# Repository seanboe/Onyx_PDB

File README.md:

# Onyx Power Distribution Board 

See the updated project in [Team Inspiration's Repository](https://github.com/InspirationRobotics/PowerDist).

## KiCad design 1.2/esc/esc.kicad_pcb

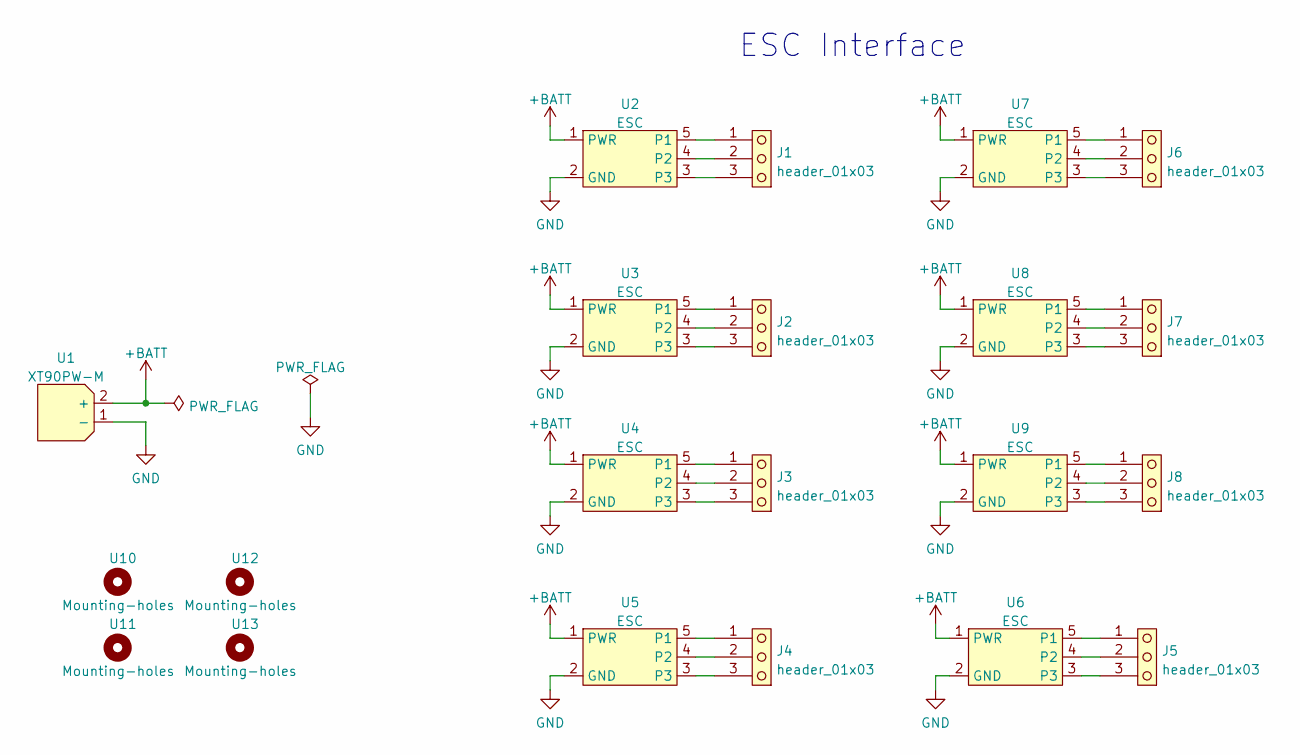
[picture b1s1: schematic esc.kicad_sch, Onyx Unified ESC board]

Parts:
J1, J2, J3, J4, J5, J6, J7, J8: header_01x03; MegaF_RAH_Single_3x5.7mm
U1: XT90PW-M; AMASS_XT90PW-M_Horizontal
U2, U3, U4, U5, U6, U7, U8, U9: ESC; esc
U10, U11, U12, U13: Mounting-holes; plated_hole_3.0x3.6mm

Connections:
+BATT: U1.2 (+), U2.1 (PWR), U3.1 (PWR), U4.1 (PWR), U5.1 (PWR), U6.1 (PWR), U7.1 (PWR), U8.1 (PWR), U9.1 (PWR)
GND: U1.1 (-), U2.2 (GND), U3.2 (GND), U4.2 (GND), U5.2 (GND), U6.2 (GND), U7.2 (GND), U8.2 (GND), U9.2 (GND)
unnamed: J1.1, U2.5 (P1)
unnamed: J1.2, U2.4 (P2)
unnamed: J1.3, U2.3
unnamed: J2.1, U3.5 (P1)
unnamed: J2.2, U3.4 (P2)
unnamed: J2.3, U3.3
unnamed: J3.1, U4.5 (P1)
unnamed: J3.2, U4.4 (P2)
unnamed: J3.3, U4.3
unnamed: J4.1, U5.5 (P1)
unnamed: J4.2, U5.4 (P2)
unnamed: J4.3, U5.3
unnamed: J5.1, U6.5 (P1)
unnamed: J5.2, U6.4 (P2)
unnamed: J5.3, U6.3
unnamed: J6.1, U7.5 (P1)
unnamed: J6.2, U7.4 (P2)
unnamed: J6.3, U7.3
unnamed: J7.1, U8.5 (P1)
unnamed: J7.2, U8.4 (P2)
unnamed: J7.3, U8.3
unnamed: J8.1, U9.5 (P1)
unnamed: J8.2, U9.4 (P2)
unnamed: J8.3, U9.3

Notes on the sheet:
ESC Interface

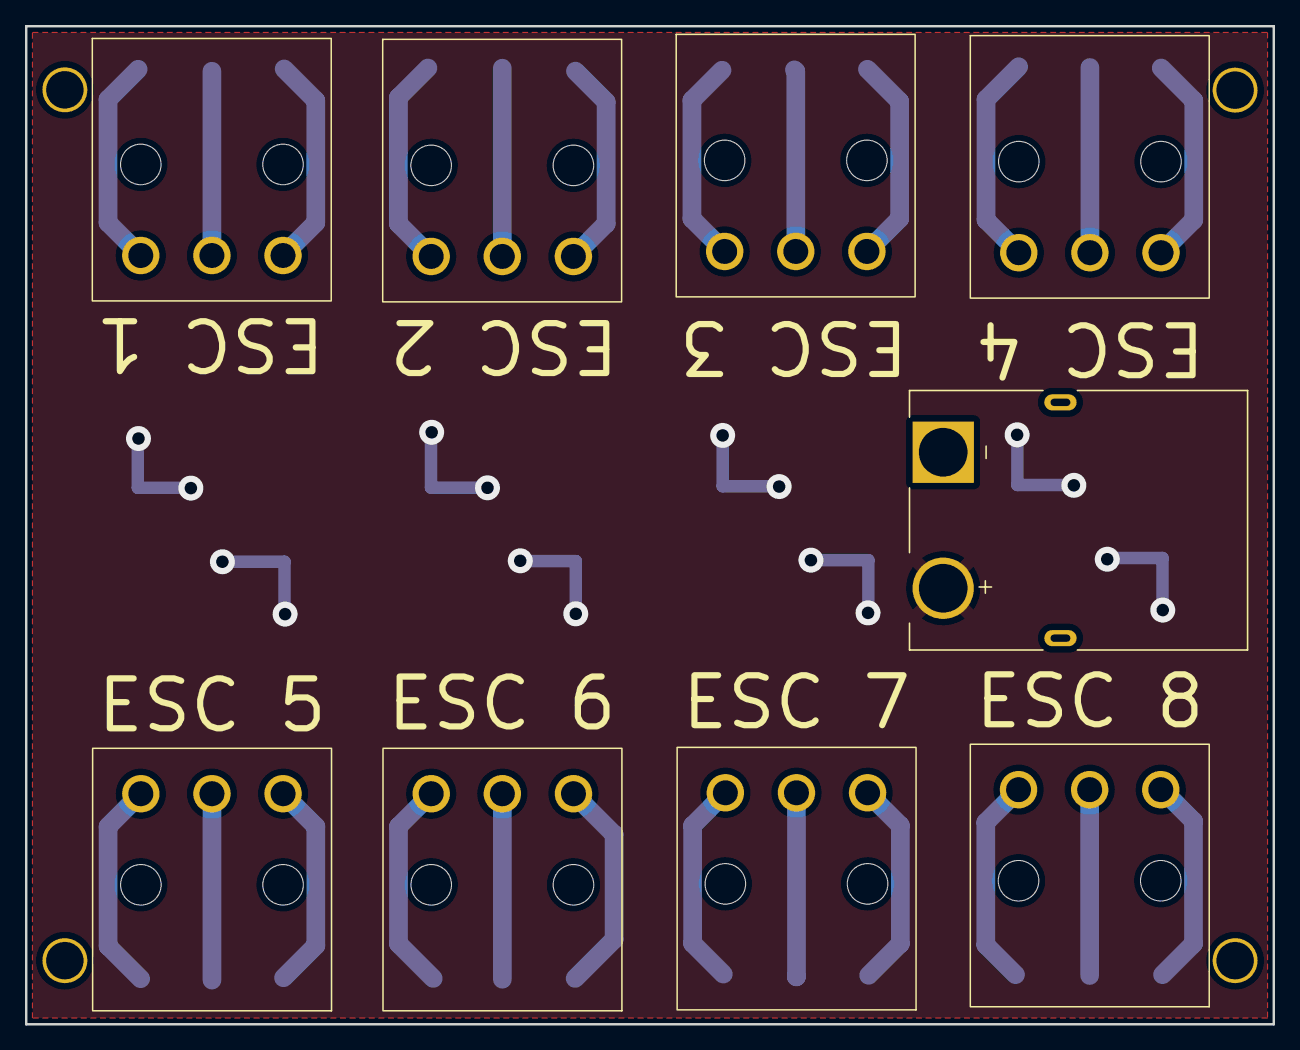
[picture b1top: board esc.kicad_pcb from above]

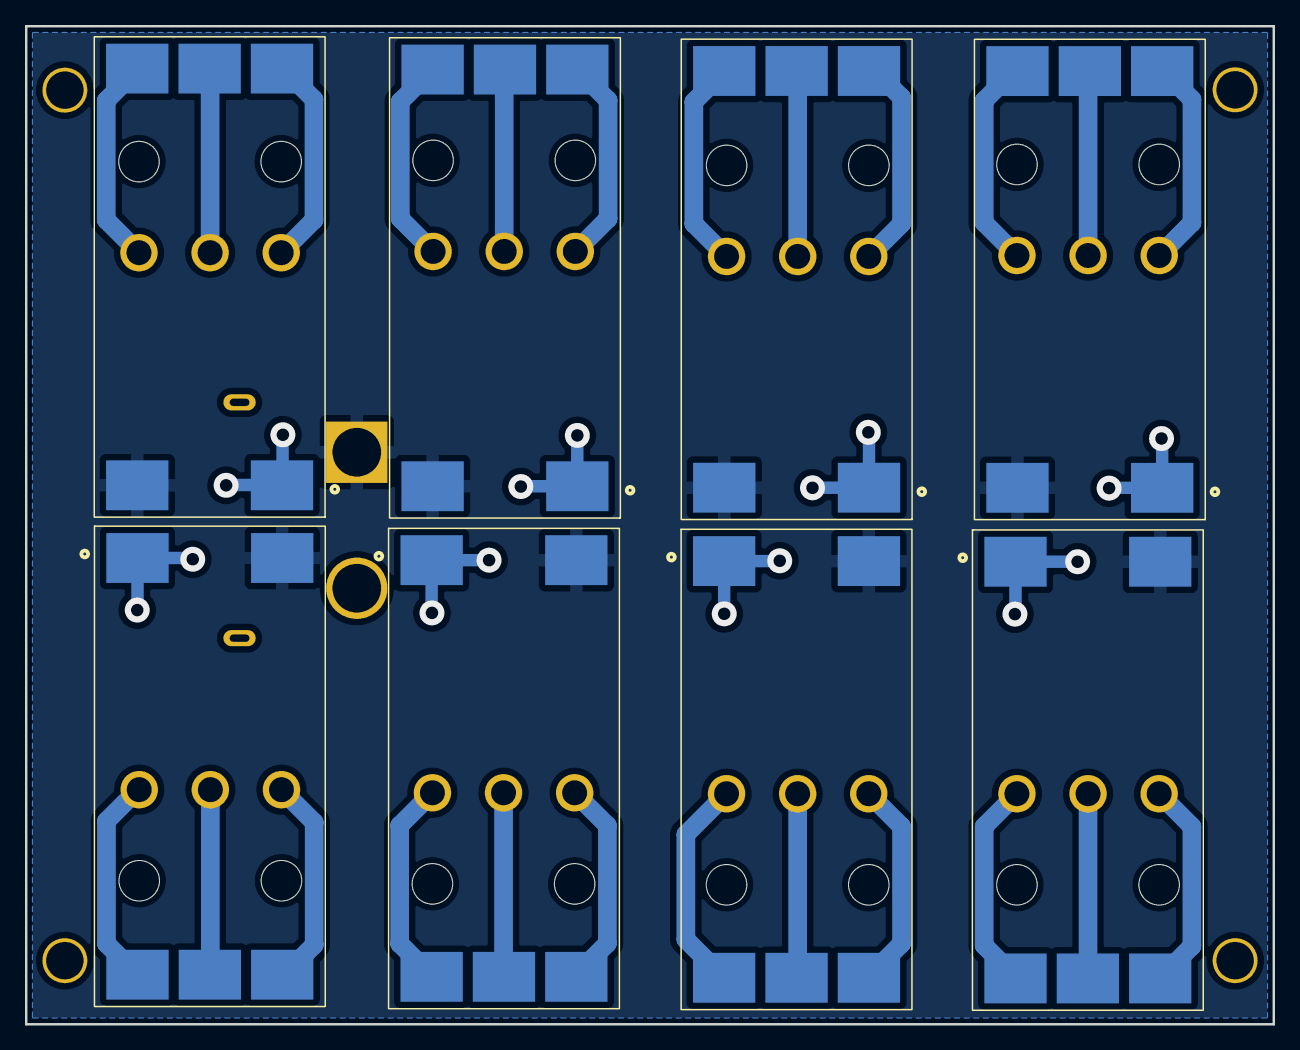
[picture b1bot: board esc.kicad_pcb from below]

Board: 2 copper layers, 100.0 x 80.0 mm, 21 parts (8 on the bottom side), 26 nets.

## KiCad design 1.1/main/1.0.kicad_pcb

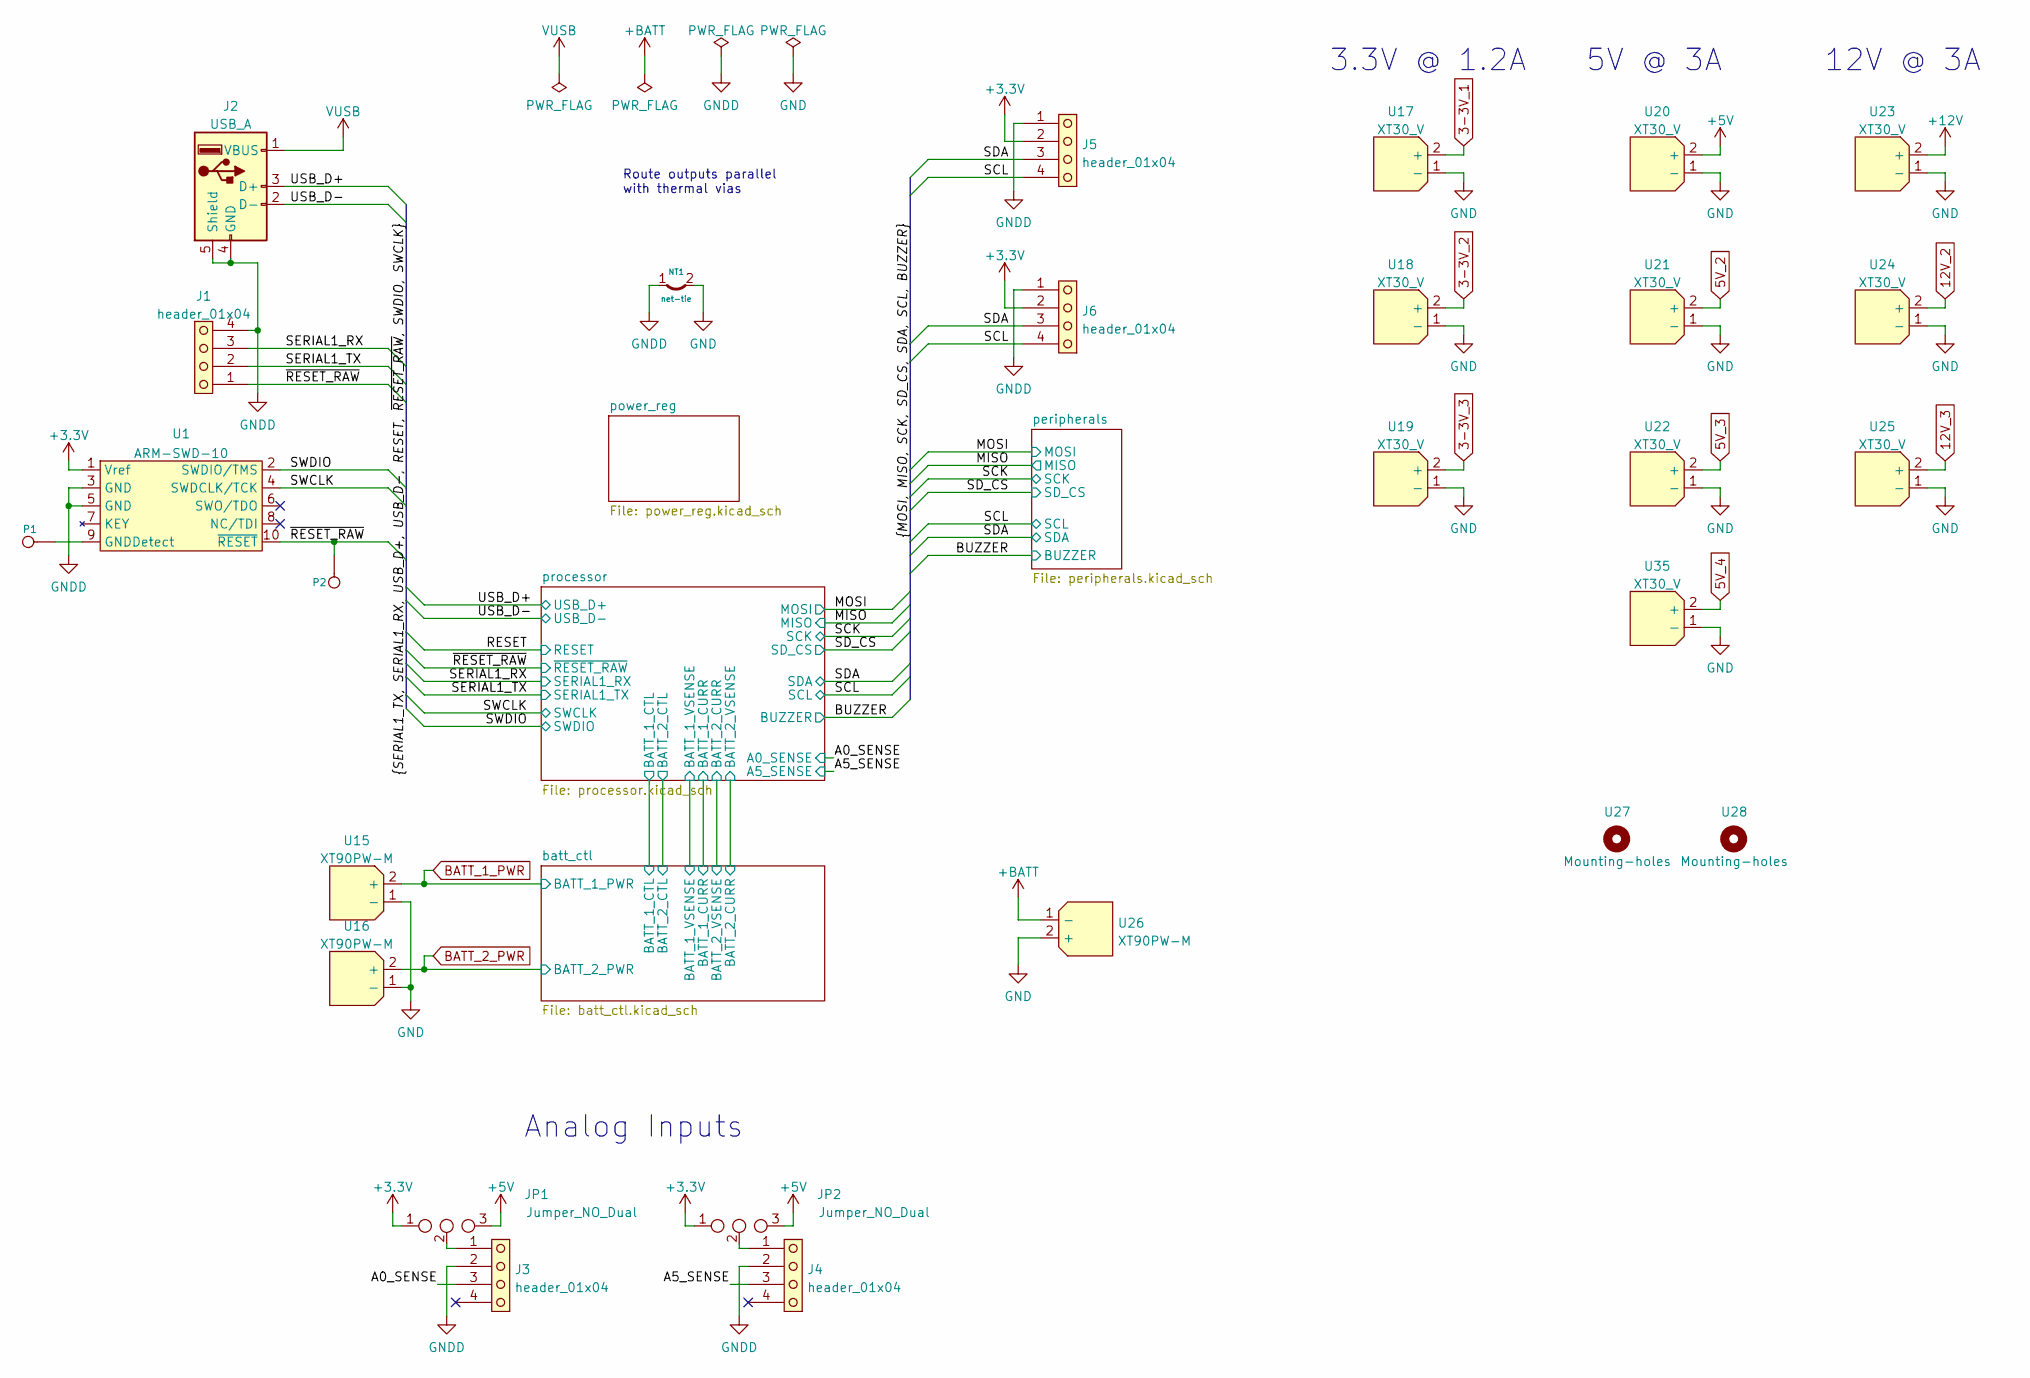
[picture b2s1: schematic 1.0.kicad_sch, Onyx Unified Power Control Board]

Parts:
J1: header_01x04; Stemma_QT_V
J2: USB_A; amphenol_micro_usb_no_flange_10118192
J3, J4, J5, J6: header_01x04; Stemma_QT_2
JP1, JP2: Jumper_NO_Dual; SolderJumper-3_P1.3mm_Open_RoundedPad1.0x1.5mm_NumberLabels
NT1: net-tie; NetTie-2_SMD_Pad2.0mm
P1, P2: CONN_1; header_01x01_tht
U1: ARM-SWD-10
U15, U16, U26: XT90PW-M; AMASS_XT90PW-M_Horizontal
U17, U18, U19, U20, U21, U22, U23, U24, U25, U35: XT30_V; AMASS_XT30U-F_1x02_P5.0mm_Vertical
U27, U28: Mounting-holes; plated_hole_3.0x3.6mm

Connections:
3-3V_1: U17.2 (+); also elsewhere on the board
3-3V_2: U18.2 (+); also elsewhere on the board
3-3V_3: U19.2 (+); also elsewhere on the board
5V_2: U21.2 (+); also elsewhere on the board
5V_3: U22.2 (+); also elsewhere on the board
12V_2: U24.2 (+); also elsewhere on the board
12V_3: U25.2 (+); also elsewhere on the board
+3V3: J5.2, J6.2, JP1.1, JP2.1, U1.1 (Vref); also elsewhere on the board
+5V: JP1.3, JP2.3, U20.2 (+); also elsewhere on the board
+12V: U23.2 (+); also elsewhere on the board
+BATT: U26.1 (-); also elsewhere on the board
/A0_SENSE: J3.3; also elsewhere on the board
/A5_SENSE: J4.3; also elsewhere on the board
/SCL: J5.4, J6.4; also elsewhere on the board
/SDA: J5.3, J6.3; also elsewhere on the board
/SERIAL1_RX: J1.3; also elsewhere on the board
/SERIAL1_TX: J1.2; also elsewhere on the board
/SWCLK: U1.4 (SWDCLK/TCK); also elsewhere on the board
/SWDIO: U1.2 (SWDIO/TMS); also elsewhere on the board
/USB_D+: J2.3 (D+); also elsewhere on the board
/USB_D-: J2.2 (D-); also elsewhere on the board
/~RESET_RAW: J1.1, P2.1, U1.10 (~RESET); also elsewhere on the board
BATT_1_PWR: U15.2 (+); also elsewhere on the board
BATT_2_PWR: U16.2 (+); also elsewhere on the board
GND: NT1.2, U15.1 (-), U16.1 (-), U17.1 (-), U18.1 (-), U19.1 (-), U20.1 (-), U21.1 (-), U22.1 (-), U23.1 (-), U24.1 (-), U25.1 (-), U26.2 (+), U35.1 (-); also elsewhere on the board
GNDD: J1.4, J2.4 (GND), J2.5 (Shield), J3.2, J4.2, J5.1, J6.1, NT1.1, U1.3 (GND), U1.5 (GND); also elsewhere on the board
unnamed: J3.1, JP1.2
unnamed: J4.1, JP2.2
unnamed: P1.1, U1.9 (GNDDetect)
VUSB: J2.1 (VBUS); also elsewhere on the board

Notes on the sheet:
12V @ 3A
Analog Inputs
Route outputs parallel with thermal vias
3.3V @ 1.2A
5V @ 3A

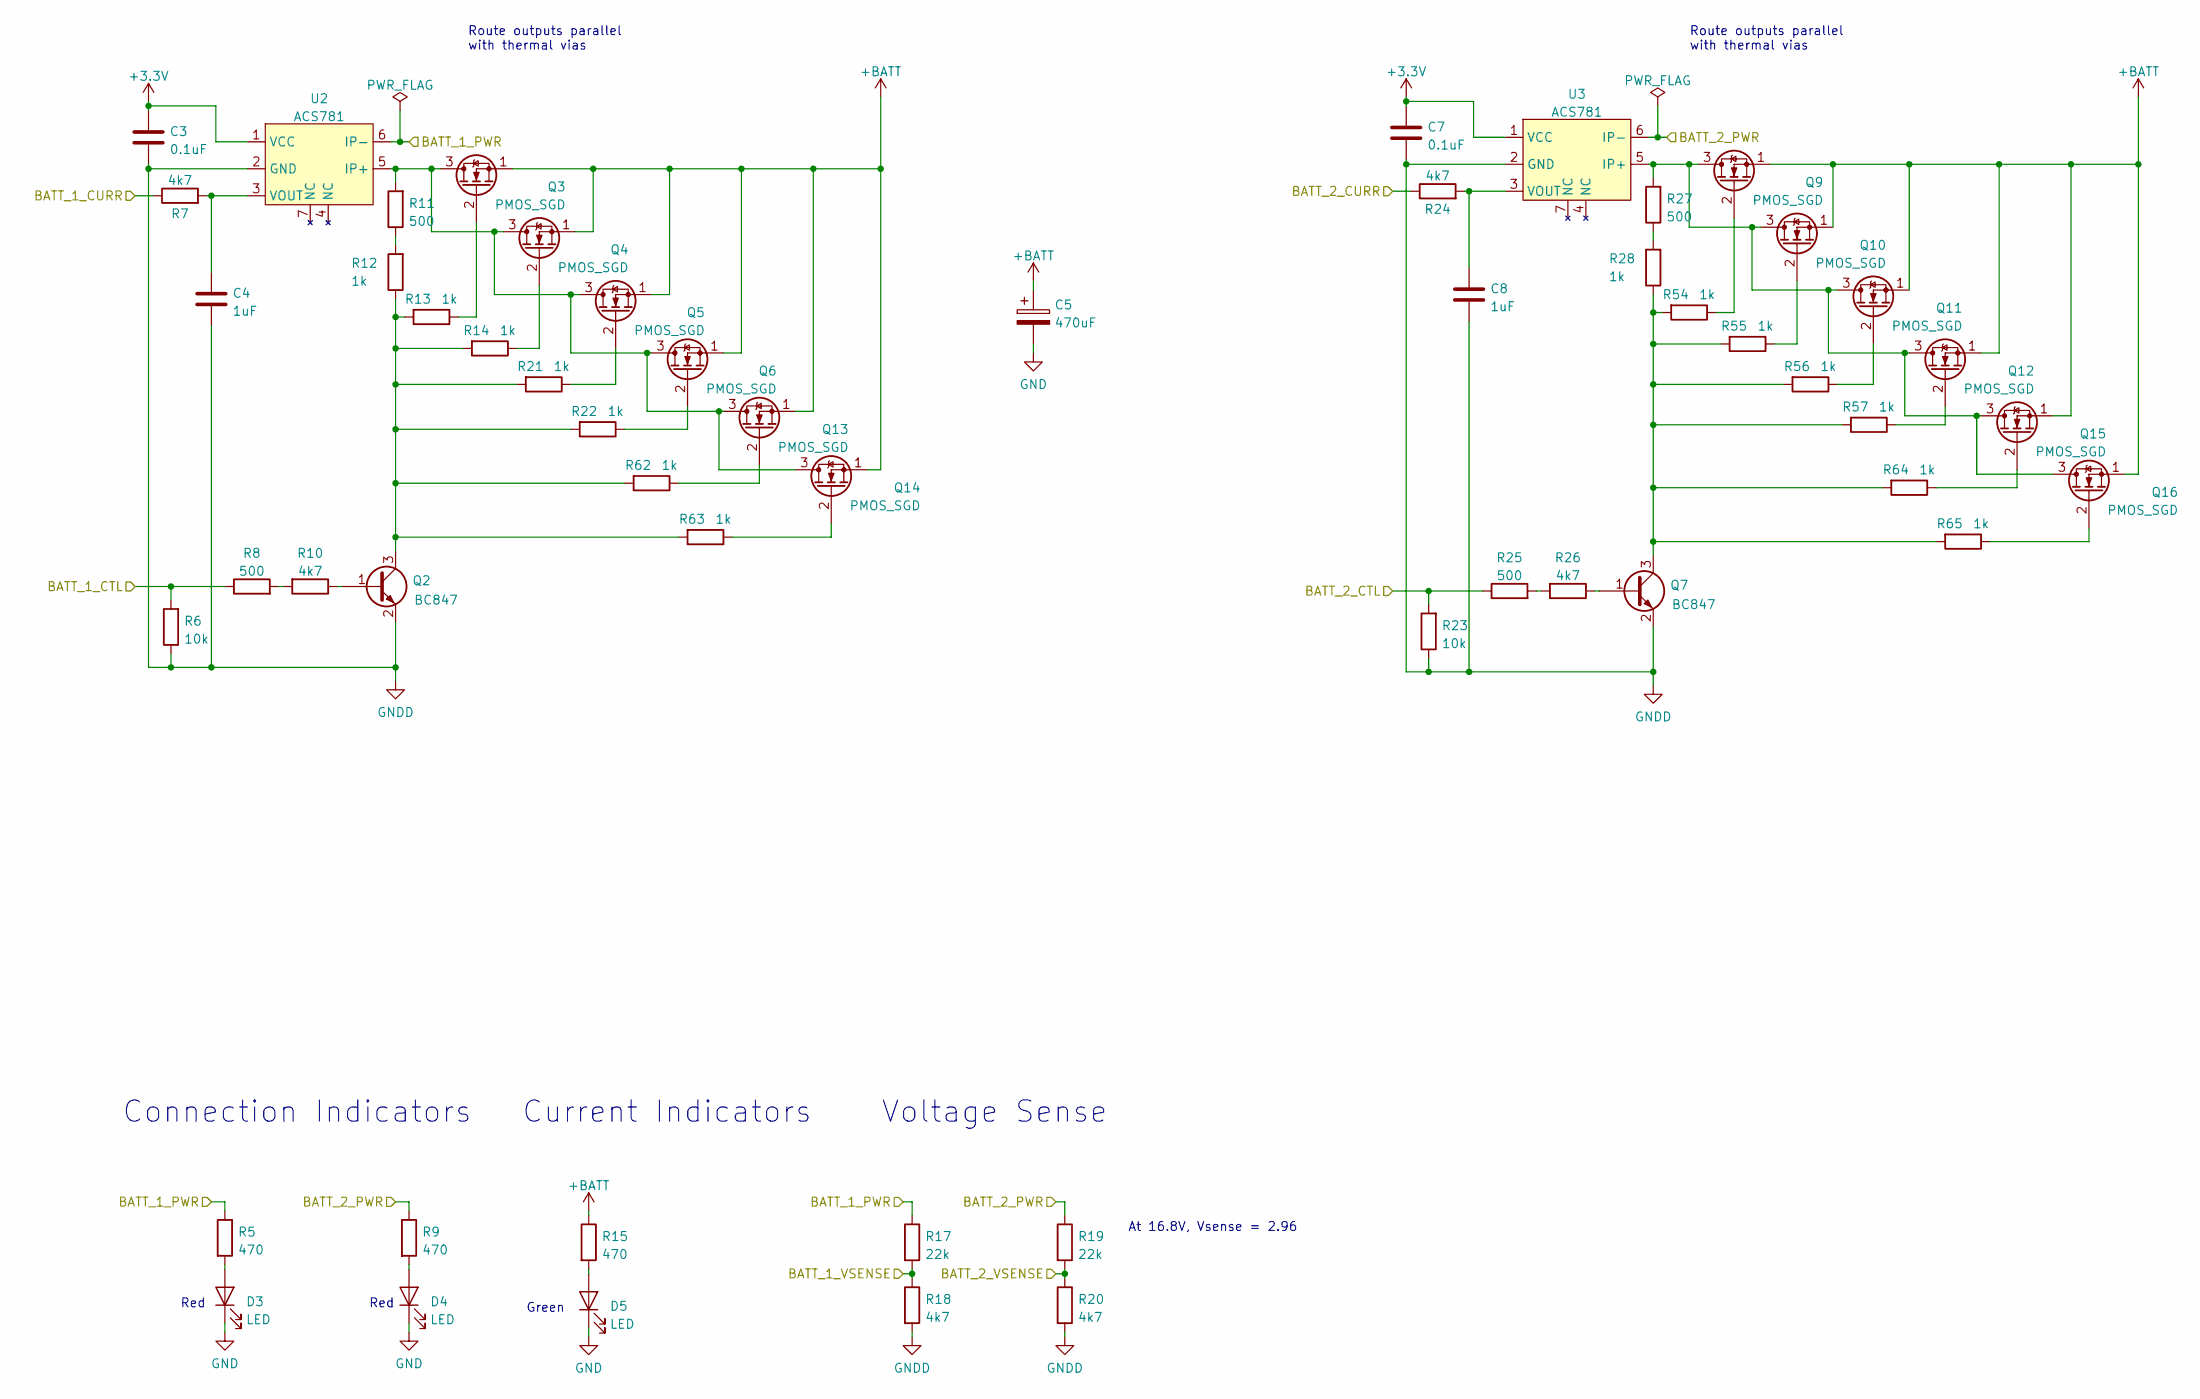
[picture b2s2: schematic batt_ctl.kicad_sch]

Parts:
C3, C7: 0.1uF; C_1608_603_B
C4, C8: 1uF; C_1608_603_B
C5: 470uF; THT_470uF_Cap
D3, D4, D5: LED; D_0603
Q2, Q7: BC847; SOT-23
Q3, Q4, Q5, Q6, Q9, Q10, Q11, Q12, Q13, Q14, Q15, Q16: PMOS_SGD; VDFN-8
R5, R9, R15: 470; R_1608_603_B
R6, R23: 10k; R_1608_603_B
R7, R10, R18, R20, R24, R26: 4k7; R_1608_603_B
R8, R11, R25, R27: 500; R_2012_805_B
R12, R13, R14, R21, R22, R28, R54, R55, R56, R57, R62, R63, R64, R65: 1k; R_1608_603_B
R17, R19: 22k; R_1608_603_B
U2, U3: ACS781; 7-LR-PSOF

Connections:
+3V3: C3.2, C7.2, U2.1 (VCC), U3.1 (VCC); also elsewhere on the board
+BATT: C5.1, Q3.1 (S), Q4.1 (S), Q5.1 (S), Q6.1 (S), Q9.1 (S), Q10.1 (S), Q11.1 (S), Q12.1 (S), Q13.1 (S), Q14.1 (S), Q15.1 (S), Q16.1 (S), R15.1; also elsewhere on the board
/batt_ctl/BATT_1_CTL: R6.2, R8.1; also elsewhere on the board
/batt_ctl/BATT_1_CURR: R7.1; also elsewhere on the board
/batt_ctl/BATT_1_VSENSE: R17.2, R18.1; also elsewhere on the board
/batt_ctl/BATT_2_CTL: R23.2, R25.1; also elsewhere on the board
/batt_ctl/BATT_2_CURR: R24.1; also elsewhere on the board
/batt_ctl/BATT_2_VSENSE: R19.2, R20.1; also elsewhere on the board
BATT_1_PWR: R5.1, R17.1, U2.6 (IP-); also elsewhere on the board
BATT_2_PWR: R9.1, R19.1, U3.6 (IP-); also elsewhere on the board
GND: C5.2, D3.1 (K), D4.1 (K), D5.1 (K); also elsewhere on the board
GNDD: C3.1, C4.1, C7.1, C8.1, Q2.2 (E), Q7.2 (E), R6.1, R18.2, R20.2, R23.1, U2.2 (GND), U3.2 (GND); also elsewhere on the board
unnamed: C4.2, R7.2, U2.3 (VOUT)
unnamed: C8.2, R24.2, U3.3 (VOUT)
unnamed: D3.2 (A), R5.2
unnamed: D4.2 (A), R9.2
unnamed: D5.2 (A), R15.2
unnamed: Q2.1 (B), R10.1
unnamed: Q2.3 (C), R12.1, R13.2, R14.2, R21.2, R22.2, R62.2, R63.2
unnamed: Q3.2 (G), R13.1
unnamed: Q4.2 (G), R14.1
unnamed: Q5.2 (G), R21.1
unnamed: Q6.2 (G), R22.1
unnamed: Q7.1 (B), R26.1
unnamed: Q7.3 (C), R28.1, R54.2, R55.2, R56.2, R57.2, R64.2, R65.2
unnamed: Q9.2 (G), R54.1
unnamed: Q10.2 (G), R55.1
unnamed: Q9.3 (D), Q10.3 (D), Q11.3 (D), Q12.3 (D), Q15.3 (D), Q16.3 (D), R27.2, U3.5 (IP+)
unnamed: Q11.2 (G), R56.1
unnamed: Q12.2 (G), R57.1
unnamed: Q13.2 (G), R62.1
unnamed: Q3.3 (D), Q4.3 (D), Q5.3 (D), Q6.3 (D), Q13.3 (D), Q14.3 (D), R11.2, U2.5 (IP+)
unnamed: Q14.2 (G), R63.1
unnamed: Q15.2 (G), R64.1
unnamed: Q16.2 (G), R65.1
unnamed: R8.2, R10.2
unnamed: R11.1, R12.2
unnamed: R25.2, R26.2
unnamed: R27.1, R28.2

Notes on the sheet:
Connection Indicators
Red
Route outputs parallel with thermal vias
Voltage Sense
Green
Current Indicators
At 16.8V, Vsense = 2.96

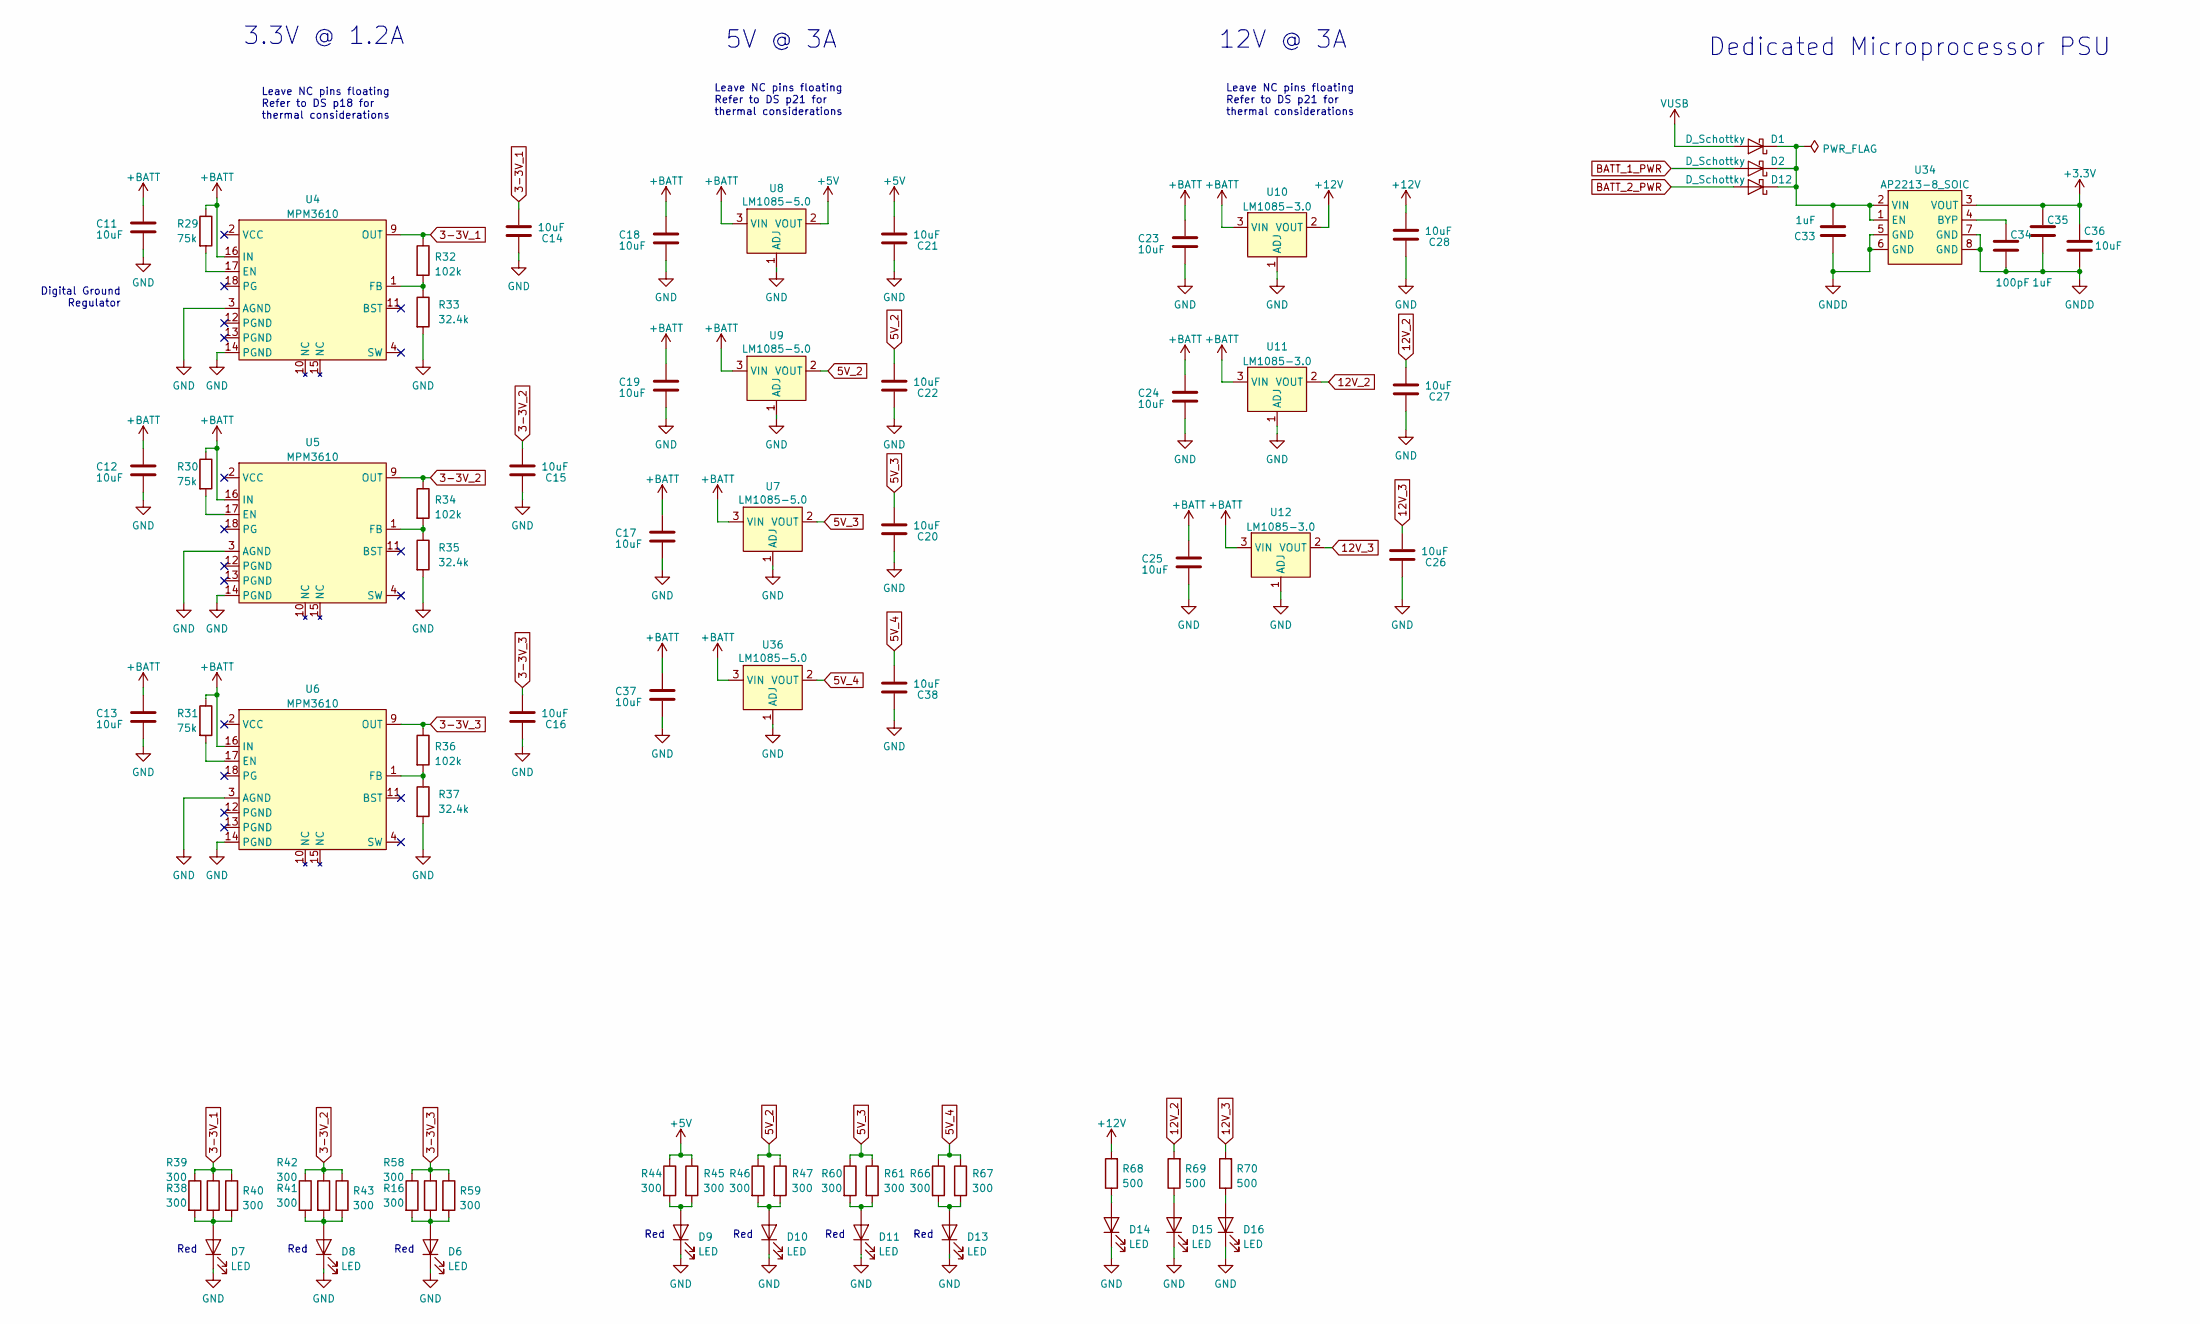
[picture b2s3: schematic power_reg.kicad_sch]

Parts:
C11, C12, C13, C17, C18, C19, C23, C24, C25, C37: 10uF; C_2012_805_B
C14, C15, C16, C20, C21, C22, C26, C27, C28, C36, C38: 10uF; C_1608_603_B
C33, C35: 1uF; C_1608_603_B; Part 0603YC105KAT2A
C34: 100pF; C_1608_603_B; Part GCG1885G1H101JA01D
D1, D2, D12: D_Schottky; D_SOD-123F; Part PMEG1030EH
D6, D7, D8, D9, D10, D11, D13, D14, D15, D16: LED; D_0603
R16, R38, R39, R40, R41, R42, R43, R44, R45, R46, R47, R58, R59, R60, R61, R66, R67: 300; R_1608_603_B
R29, R30, R31: 75k; R_1608_603_B
R32, R34, R36: 102k; R_1608_603_B
R33, R35, R37: 32.4k; R_1608_603_B
R68, R69, R70: 500; R_2012_805_B
U4, U5, U6: MPM3610; 20-PowerLQFN
U7, U8, U9, U36: LM1085-5.0; TO-263-3_TabPin2
U10, U11, U12: LM1085-3.0; TO-263-3_TabPin2
U34: AP2213-8_SOIC; SOIC-8_3.9x4.9mm_P1.27mm

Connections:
3-3V_1: C14.1, R32.1, R38.1, R39.1, R40.1, U4.9 (OUT); also elsewhere on the board
3-3V_2: C15.1, R34.1, R41.1, R42.1, R43.1, U5.9 (OUT); also elsewhere on the board
3-3V_3: C16.1, R16.1, R36.1, R58.1, R59.1, U6.9 (OUT); also elsewhere on the board
5V_2: C22.1, R46.1, R47.1, U9.2 (VOUT); also elsewhere on the board
5V_3: C20.1, R60.1, R61.1, U7.2 (VOUT); also elsewhere on the board
5V_4: C38.1, R66.1, R67.1, U36.2 (VOUT)
12V_2: C27.1, R69.2, U11.2 (VOUT); also elsewhere on the board
12V_3: C26.1, R70.2, U12.2 (VOUT); also elsewhere on the board
+3V3: C35.1, C36.1, U34.3 (VOUT); also elsewhere on the board
+5V: C21.1, R44.1, R45.1, U8.2 (VOUT); also elsewhere on the board
+12V: C28.1, R68.2, U10.2 (VOUT); also elsewhere on the board
+BATT: C11.1, C12.1, C13.1, C17.1, C18.1, C19.1, C23.1, C24.1, C25.1, C37.1, R29.1, R30.1, R31.1, U4.16 (IN), U5.16 (IN), U6.16 (IN), U7.3 (VIN), U8.3 (VIN), U9.3 (VIN), U10.3 (VIN), U11.3 (VIN), U12.3 (VIN), U36.3 (VIN); also elsewhere on the board
BATT_1_PWR: D2.2 (A); also elsewhere on the board
BATT_2_PWR: D12.2 (A); also elsewhere on the board
GND: C11.2, C12.2, C13.2, C14.2, C15.2, C16.2, C17.2, C18.2, C19.2, C20.2, C21.2, C22.2, C23.2, C24.2, C25.2, C26.2, C27.2, C28.2, C37.2, C38.2, D6.1 (K), D7.1 (K), D8.1 (K), D9.1 (K), D10.1 (K), D11.1 (K), D13.1 (K), D14.1 (K), D15.1 (K), D16.1 (K), R33.2, R35.2, R37.2, U4.3 (AGND), U4.14 (PGND), U5.3 (AGND), U5.14 (PGND), U6.3 (AGND), U6.14 (PGND), U7.1 (ADJ), U8.1 (ADJ), U9.1 (ADJ), U10.1 (ADJ), U11.1 (ADJ), U12.1 (ADJ), U36.1 (ADJ); also elsewhere on the board
GNDD: C33.1, C34.2, C35.2, C36.2, U34.5 (GND), U34.6 (GND), U34.7 (GND), U34.8 (GND); also elsewhere on the board
unnamed: C33.2, D1.1 (K), D2.1 (K), D12.1 (K), U34.1 (EN), U34.2 (VIN)
unnamed: C34.1, U34.4 (BYP)
unnamed: D6.2 (A), R16.2, R58.2, R59.2
unnamed: D7.2 (A), R38.2, R39.2, R40.2
unnamed: D8.2 (A), R41.2, R42.2, R43.2
unnamed: D9.2 (A), R44.2, R45.2
unnamed: D10.2 (A), R46.2, R47.2
unnamed: D11.2 (A), R60.2, R61.2
unnamed: D13.2 (A), R66.2, R67.2
unnamed: D14.2 (A), R68.1
unnamed: D15.2 (A), R69.1
unnamed: D16.2 (A), R70.1
unnamed: R29.2, U4.17 (EN)
unnamed: R30.2, U5.17 (EN)
unnamed: R31.2, U6.17 (EN)
unnamed: R32.2, R33.1, U4.1 (FB)
unnamed: R34.2, R35.1, U5.1 (FB)
unnamed: R36.2, R37.1, U6.1 (FB)
VUSB: D1.2 (A); also elsewhere on the board

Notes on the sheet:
Leave NC pins floating Refer to DS p21 for thermal considerations
Red
12V @ 3A
3.3V @ 1.2A
Digital Ground Regulator
5V @ 3A
Dedicated Microprocessor PSU
Leave NC pins floating Refer to DS p18 for thermal considerations

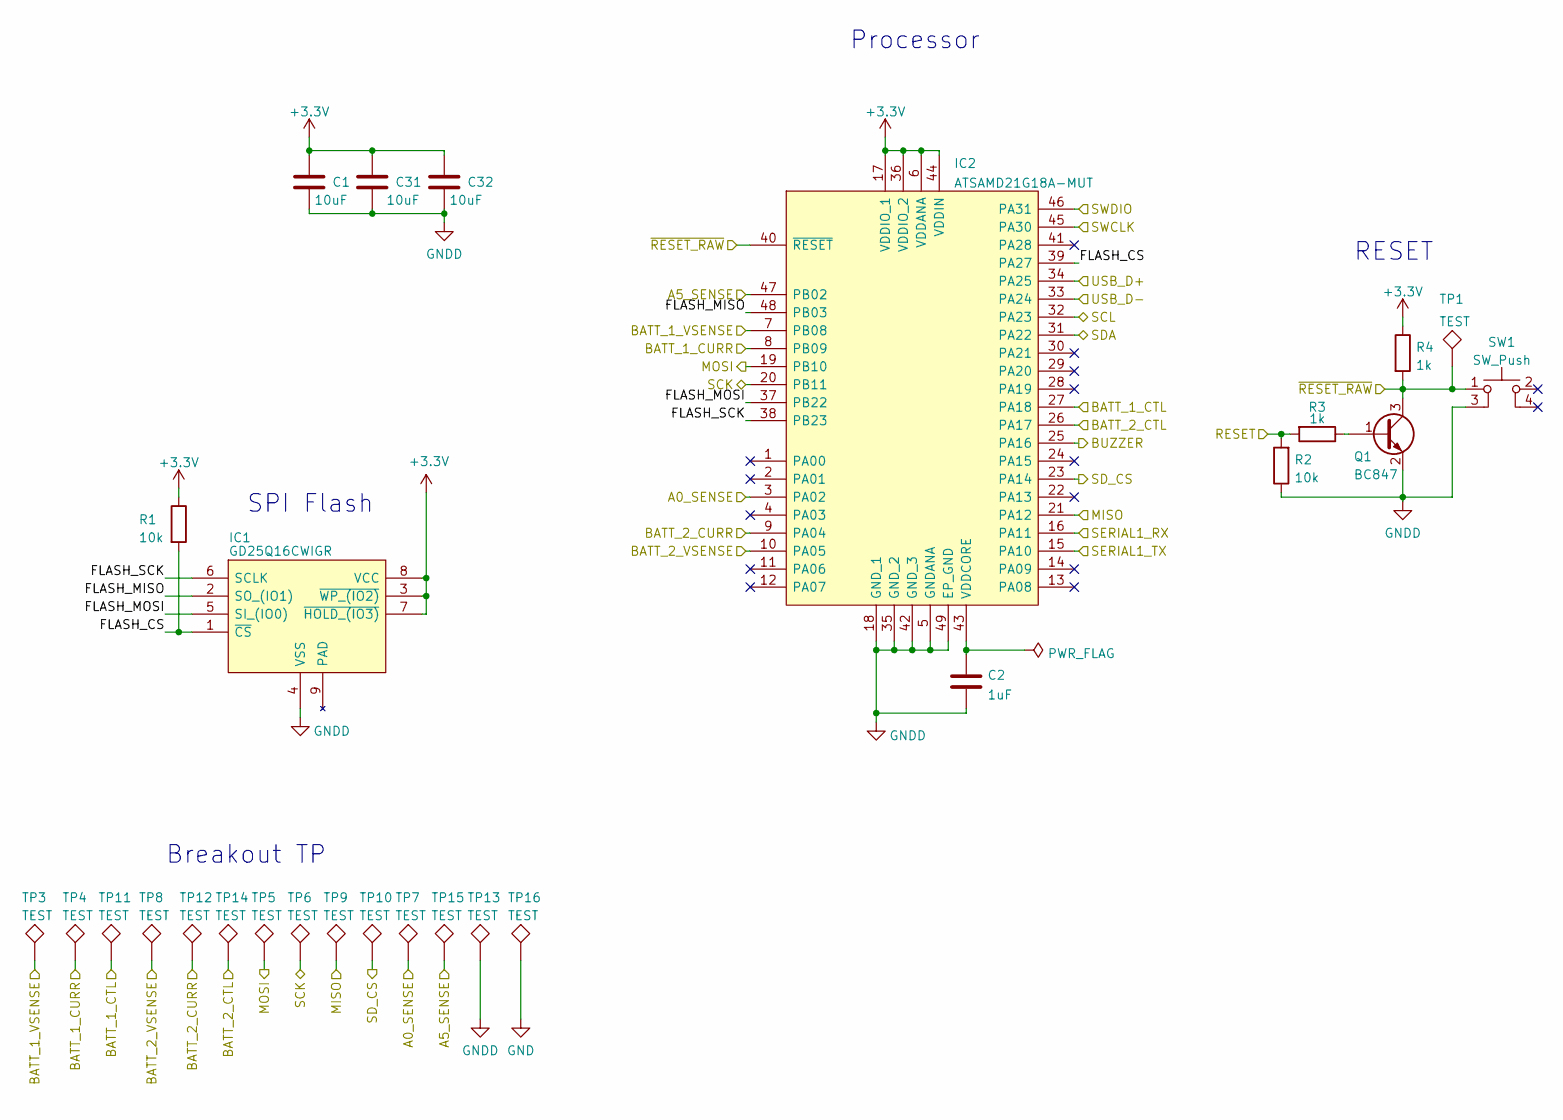
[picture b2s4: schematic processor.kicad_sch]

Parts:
C1, C31, C32: 10uF; C_1608_603_B
C2: 1uF; C_1608_603_B; Part 0603YC105KAT2A
IC1: GD25Q16CWIGR; SOIC-8_3.9x4.9mm_P1.27mm
IC2: ATSAMD21G18A-MUT; QFN50P700X700X90-49N-D
Q1: BC847; SOT-23
R1, R2: 10k; R_1608_603_B
R3, R4: 1k; R_1608_603_B
SW1: SW_Push; KMR243GLFG
TP1: TEST; test_point_1.0mm_square
TP3, TP4, TP5, TP6, TP7, TP8, TP9, TP10, TP11, TP12, TP13, TP14, TP15, TP16: TEST; test_point_2mm_square

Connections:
+3V3: C1.1, C31.1, C32.1, IC1.3 (~WP_(IO2)), IC1.7 (~HOLD_(IO3)), IC1.8 (VCC), IC2.6 (VDDANA), IC2.17 (VDDIO_1), IC2.36 (VDDIO_2), IC2.44 (VDDIN), R1.1, R4.1; also elsewhere on the board
/A0_SENSE: IC2.3 (PA02), TP7.1; also elsewhere on the board
/A5_SENSE: IC2.47 (PB02), TP15.1; also elsewhere on the board
/BUZZER: IC2.25 (PA16); also elsewhere on the board
/MISO: IC2.21 (PA12), TP9.1; also elsewhere on the board
/MOSI: IC2.19 (PB10), TP5.1; also elsewhere on the board
/RESET: R2.2, R3.2
/SCK: IC2.20 (PB11), TP6.1; also elsewhere on the board
/SCL: IC2.32 (PA23); also elsewhere on the board
/SDA: IC2.31 (PA22); also elsewhere on the board
/SD_CS: IC2.23 (PA14), TP10.1; also elsewhere on the board
/SERIAL1_RX: IC2.16 (PA11); also elsewhere on the board
/SERIAL1_TX: IC2.15 (PA10); also elsewhere on the board
/SWCLK: IC2.45 (PA30); also elsewhere on the board
/SWDIO: IC2.46 (PA31); also elsewhere on the board
/USB_D+: IC2.34 (PA25); also elsewhere on the board
/USB_D-: IC2.33 (PA24); also elsewhere on the board
/batt_ctl/BATT_1_CTL: IC2.27 (PA18), TP11.1; also elsewhere on the board
/batt_ctl/BATT_1_CURR: IC2.8 (PB09), TP4.1; also elsewhere on the board
/batt_ctl/BATT_1_VSENSE: IC2.7 (PB08), TP3.1; also elsewhere on the board
/batt_ctl/BATT_2_CTL: IC2.26 (PA17), TP14.1; also elsewhere on the board
/batt_ctl/BATT_2_CURR: IC2.10 (PA05), TP8.1; also elsewhere on the board
/batt_ctl/BATT_2_VSENSE: IC2.9 (PA04), TP12.1; also elsewhere on the board
/processor/FLASH_CS: IC1.1 (~CS), IC2.39 (PA27), R1.2
/processor/FLASH_MISO: IC1.2 (SO_(IO1)), IC2.48 (PB03)
/processor/FLASH_MOSI: IC1.5 (SI_(IO0)), IC2.37 (PB22)
/processor/FLASH_SCK: IC1.6 (SCLK), IC2.38 (PB23)
/~RESET_RAW: IC2.40 (~RESET), Q1.3 (C), R4.2, SW1.1, TP1.1; also elsewhere on the board
GND: TP16.1; also elsewhere on the board
GNDD: C1.2, C2.2, C31.2, C32.2, IC1.4 (VSS), IC2.5 (GNDANA), IC2.18 (GND_1), IC2.35 (GND_2), IC2.42 (GND_3), IC2.49 (EP_GND), Q1.2 (E), R2.1, SW1.3, TP13.1; also elsewhere on the board
unnamed: C2.1, IC2.43 (VDDCORE)
unnamed: Q1.1 (B), R3.1

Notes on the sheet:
SPI Flash
RESET
Breakout TP
Processor
